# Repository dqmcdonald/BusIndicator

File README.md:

# BusIndicator
Buffered LED indicator, pulldown and input for 8-Bit bus

Used for 8-Bit computer and similar bread-board projects.

D. Q. McDonald
May 2026

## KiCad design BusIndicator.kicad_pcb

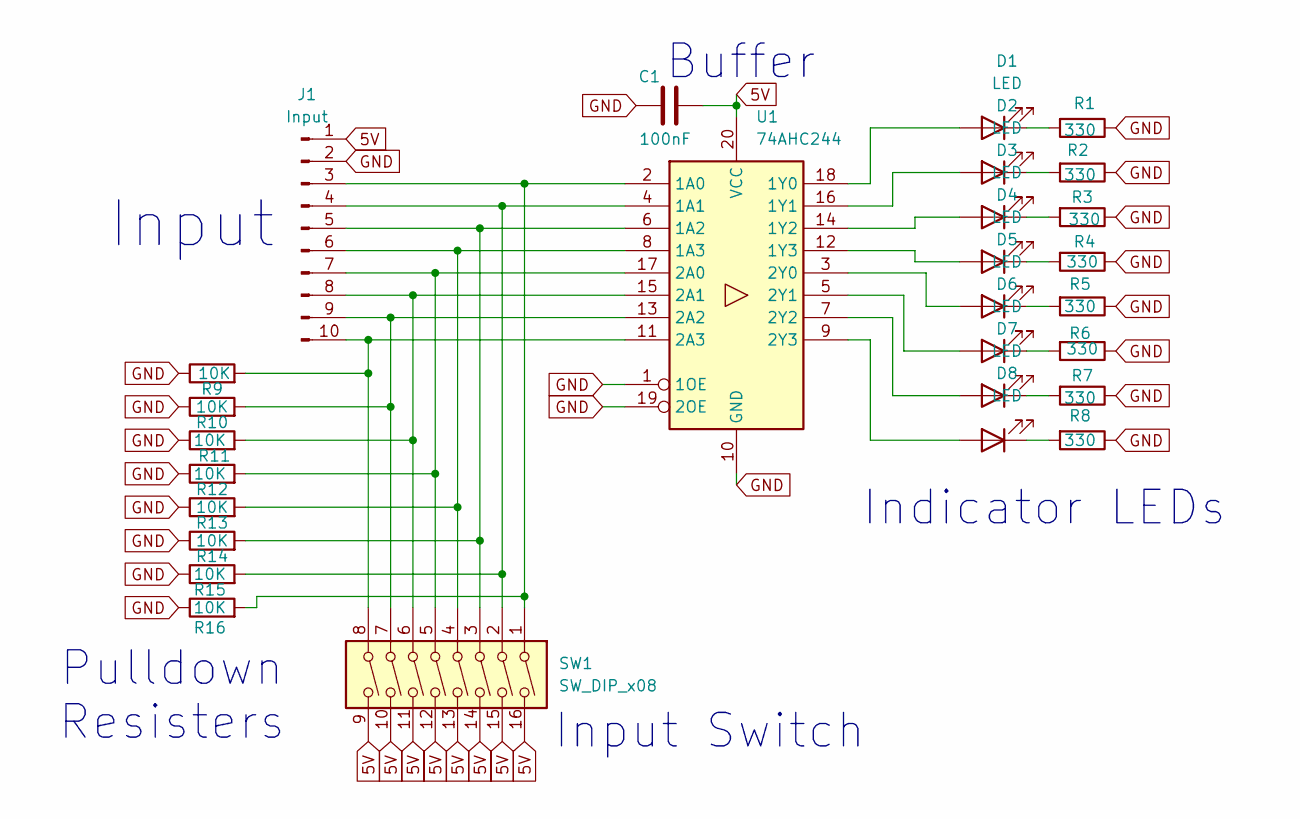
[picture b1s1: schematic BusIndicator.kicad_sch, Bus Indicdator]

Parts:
C1: 100nF; C_0805_2012Metric_Pad1.18x1.45mm_HandSolder
D1, D2, D3, D4, D5, D6, D7, D8: LED; LED_0805_2012Metric_Pad1.15x1.40mm_HandSolder
J1: Input; PinHeader_1x10_P2.54mm_Vertical
R1, R2, R3, R4, R5, R6, R7, R8: 330; R_0805_2012Metric_Pad1.20x1.40mm_HandSolder
R9, R10, R11, R12, R13, R14, R15, R16: 10K; R_0805_2012Metric_Pad1.20x1.40mm_HandSolder
SW1: SW_DIP_x08; DIP-16_W7.62mm_Socket_LongPads
U1: 74AHC244; DIP-20_W7.62mm_LongPads

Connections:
5V: C1.2, J1.1, SW1.9, SW1.10, SW1.11, SW1.12, SW1.13, SW1.14, SW1.15, SW1.16, U1.20 (VCC)
GND: C1.1, J1.2, R1.1, R2.1, R3.1, R4.1, R5.1, R6.1, R7.1, R8.1, R9.1, R10.1, R11.1, R12.1, R13.1, R14.1, R15.1, R16.1, U1.1 (1OE), U1.10 (GND), U1.19 (2OE)
unnamed: D1.2 (A), U1.18 (1Y0)
unnamed: D1.1 (K), R1.2
unnamed: D2.2 (A), U1.16 (1Y1)
unnamed: D2.1 (K), R2.2
unnamed: D3.2 (A), U1.14 (1Y2)
unnamed: D3.1 (K), R3.2
unnamed: D4.2 (A), U1.12 (1Y3)
unnamed: D4.1 (K), R4.2
unnamed: D5.2 (A), U1.3 (2Y0)
unnamed: D5.1 (K), R5.2
unnamed: D6.2 (A), U1.5 (2Y1)
unnamed: D6.1 (K), R6.2
unnamed: D7.2 (A), U1.7 (2Y2)
unnamed: D7.1 (K), R7.2
unnamed: D8.2 (A), U1.9 (2Y3)
unnamed: D8.1 (K), R8.2
unnamed: J1.3, R16.2, SW1.1, U1.2 (1A0)
unnamed: J1.4, R15.2, SW1.2, U1.4 (1A1)
unnamed: J1.5, R14.2, SW1.3, U1.6 (1A2)
unnamed: J1.6, R13.2, SW1.4, U1.8 (1A3)
unnamed: J1.7, R12.2, SW1.5, U1.17 (2A0)
unnamed: J1.8, R11.2, SW1.6, U1.15 (2A1)
unnamed: J1.9, R10.2, SW1.7, U1.13 (2A2)
unnamed: J1.10, R9.2, SW1.8, U1.11 (2A3)

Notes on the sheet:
Input Switch
Indicator LEDs
Buffer
Pulldown Resisters
Input

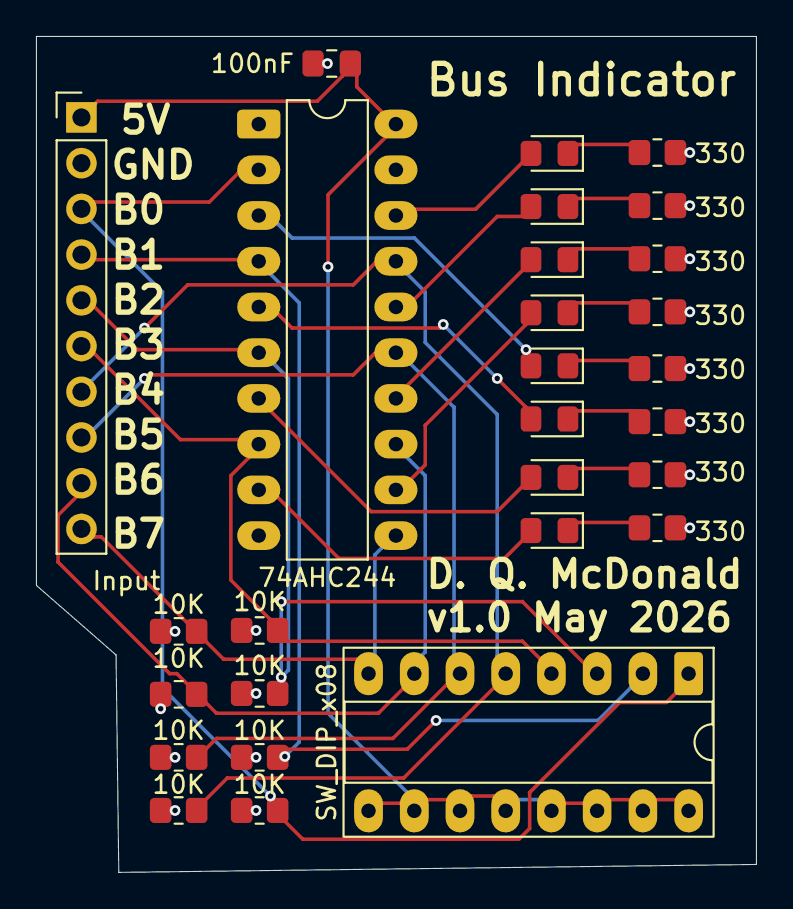
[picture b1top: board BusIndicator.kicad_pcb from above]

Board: 2 copper layers, 40.0 x 46.4 mm, 28 parts (0 on the bottom side), 26 nets.

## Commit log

2026-05-24 First complete version of the schematic and PCB layout.
2026-05-24 Small update to README.md
2026-06-03 First completely routed version of the Board, ready for review.
2026-06-03 Added PyAutoRoute ini file.
2026-06-06 Changed DIP switch to THT footprint.
